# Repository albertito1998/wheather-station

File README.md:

## Table of Contents

- [Description](#description)
- [Programming](#programming)
- [About me](#about)
- [Support](#support)
- [License](#license)

---

## Description

This report will include the entire process carried out for the design and construction of a prototype of a meteorological station where data on different environmental variables will be collected for subsequent analysis.

The creation of the prototype, the different electronic components needed, the communications infrastructure, the necessary programming code and the creation of a user interface will be discussed in order to view the data collected on a web page.

The project has been carried out in a self-taught way thanks to the material provided by the Library of the Carlos III University of Madrid and the Internet and consultations made to professors, under the supervision of my TFM professor.

 * [See The complete master thesis:](-------) - Bachelor Thesis uploaded in format PDF.
 
 * [Electrical design:](https://github.com/albertito1998/wheather-station/tree/master/Eagle) - Electrical connections.

## Programming
 * [C++](https://isocpp.org/) - Programming language.
 * [JavaScript](https://www.javascript.com/) - Programming language.
 * [Bootstrap - HTML5](https://getbootstrap.com/) - A modern responsive front-end framework
 * [Firebase](https://firebase.google.com/?hl=es-419) - Google Cloud Platform

## Microprocessors and communication
 * [Esp32](https://www.espressif.com/en/products/socs/esp32) - Espressif
* [Lora](https://heltec.org/) - Heltec

## Sensors
- BMP180
- CCS811
- INA226
- DHT22
- RAIN GAUGE AND ANEMOMETER

**Real Data Display**
Thanks to the Firebase ICloud platform, data can be displayed in dynamic charts using its Realtime Database utility.

## Website
[Go to the website!! ](https://wheather-station-18cb0.web.app/)

## About 

Industrial engineering student at Carlos III University. Passion for technology, especially electronics, programming and the world of IoT!. See my CV in the following link: [CV ](https://github.com/albertito1998/SeedbedwebsiteApp/blob/master/photos/Alberto%20G%C3%B3mez%20Zueco.pdf)

## Support

Reach out to me at one of the following places!

- Linkedin at <a href="https://www.linkedin.com/in/alberto-gomez-zueco-995538179/" target="_blank">`Linkedin`</a>
- Instagram at <a href="https://www.instagram.com/alber_gz/" target="_blank">`Instagram`</a>

---

## License

- **[MIT license](http://opensource.org/licenses/mit-license.php)**
- Copyright 2022 © <a href="/LICENSE" target="_blank">MIT LICENSE ALBERTO GÓMEZ</a>.

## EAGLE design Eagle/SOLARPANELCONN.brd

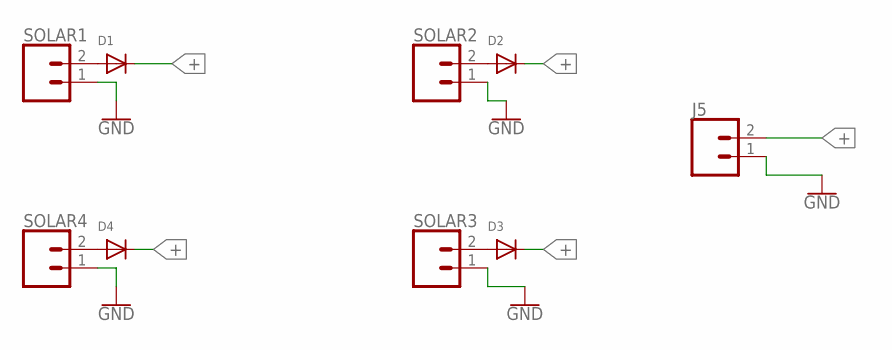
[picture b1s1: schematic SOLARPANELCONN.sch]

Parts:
D1, D2, D3, D4: DIODESOD-123; SOD-123
J5: CONN_02; 1X02
SOLAR1, SOLAR2, SOLAR3, SOLAR4: CONN_02; 1X02

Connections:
+: D1.C, D2.C, D3.C, D4.C, J5.2
GND: J5.1, SOLAR1.1, SOLAR2.1, SOLAR3.1, SOLAR4.1
unnamed: D1.A, SOLAR1.2
unnamed: D4.A, SOLAR4.2
unnamed: D3.A, SOLAR3.2
unnamed: D2.A, SOLAR2.2

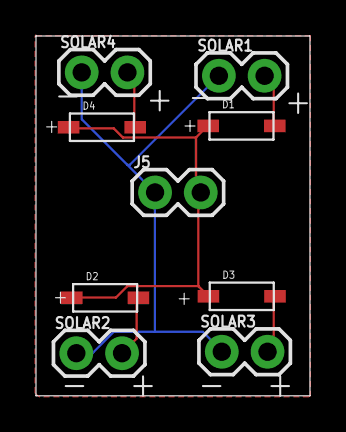
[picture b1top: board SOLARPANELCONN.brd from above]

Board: 2 copper layers, 15.2 x 20.0 mm, 9 parts (0 on the bottom side), 6 nets.

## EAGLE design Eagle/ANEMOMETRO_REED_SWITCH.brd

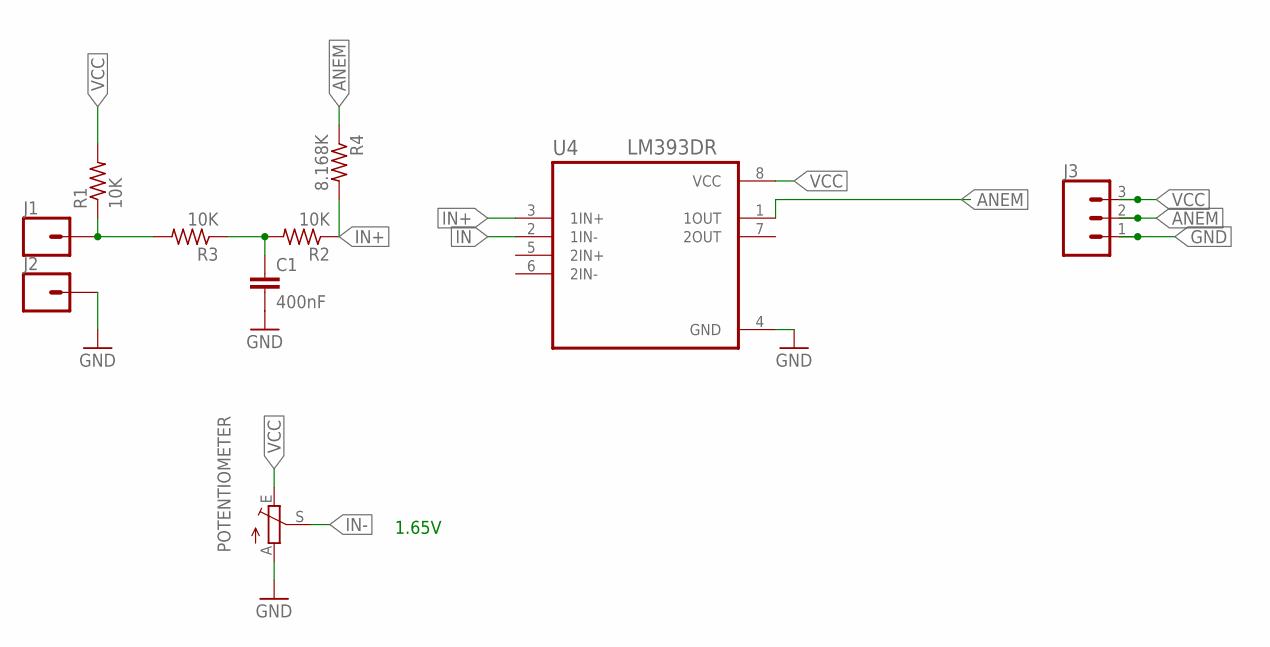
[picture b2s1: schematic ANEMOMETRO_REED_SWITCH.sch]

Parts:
C1: 400nF; C0603
J1, J2: CONN_01PTH_NO_SILK_YES_STOP; 1X01_NO_SILK
J3: CONN_03JST-PTH-VERT; JST-3-PTH-VERT
POTENTIOMETER: TRIM_EU-S64W; S64W
R1, R2, R3: 10K; R0603
R4: 8.168K; R0603
U4: LM393DR; SOIC127P599X175-8N

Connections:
ANEM: J3.2, R4.1, U4.1 (1OUT)
GND: C1.2, J2.1, J3.1, POTENTIOMETER.A, U4.4 (GND)
IN: U4.2 (1IN-)
IN+: R2.1, R4.2, U4.3 (1IN+)
IN-: POTENTIOMETER.S
unnamed: C1.1, R2.2, R3.1
unnamed: J1.1, R1.1, R3.2
VCC: J3.3, POTENTIOMETER.E, R1.2, U4.8 (VCC)

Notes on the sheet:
1.65V

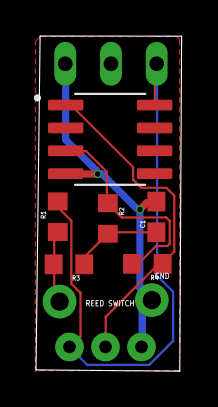
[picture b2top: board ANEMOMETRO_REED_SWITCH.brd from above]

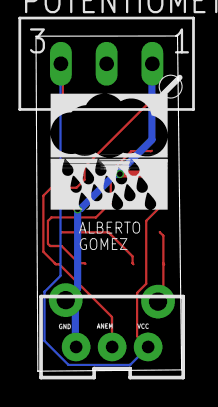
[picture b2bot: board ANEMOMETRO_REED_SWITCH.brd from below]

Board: 2 copper layers, 8.1 x 18.6 mm, 10 parts (2 on the bottom side), 6 nets.

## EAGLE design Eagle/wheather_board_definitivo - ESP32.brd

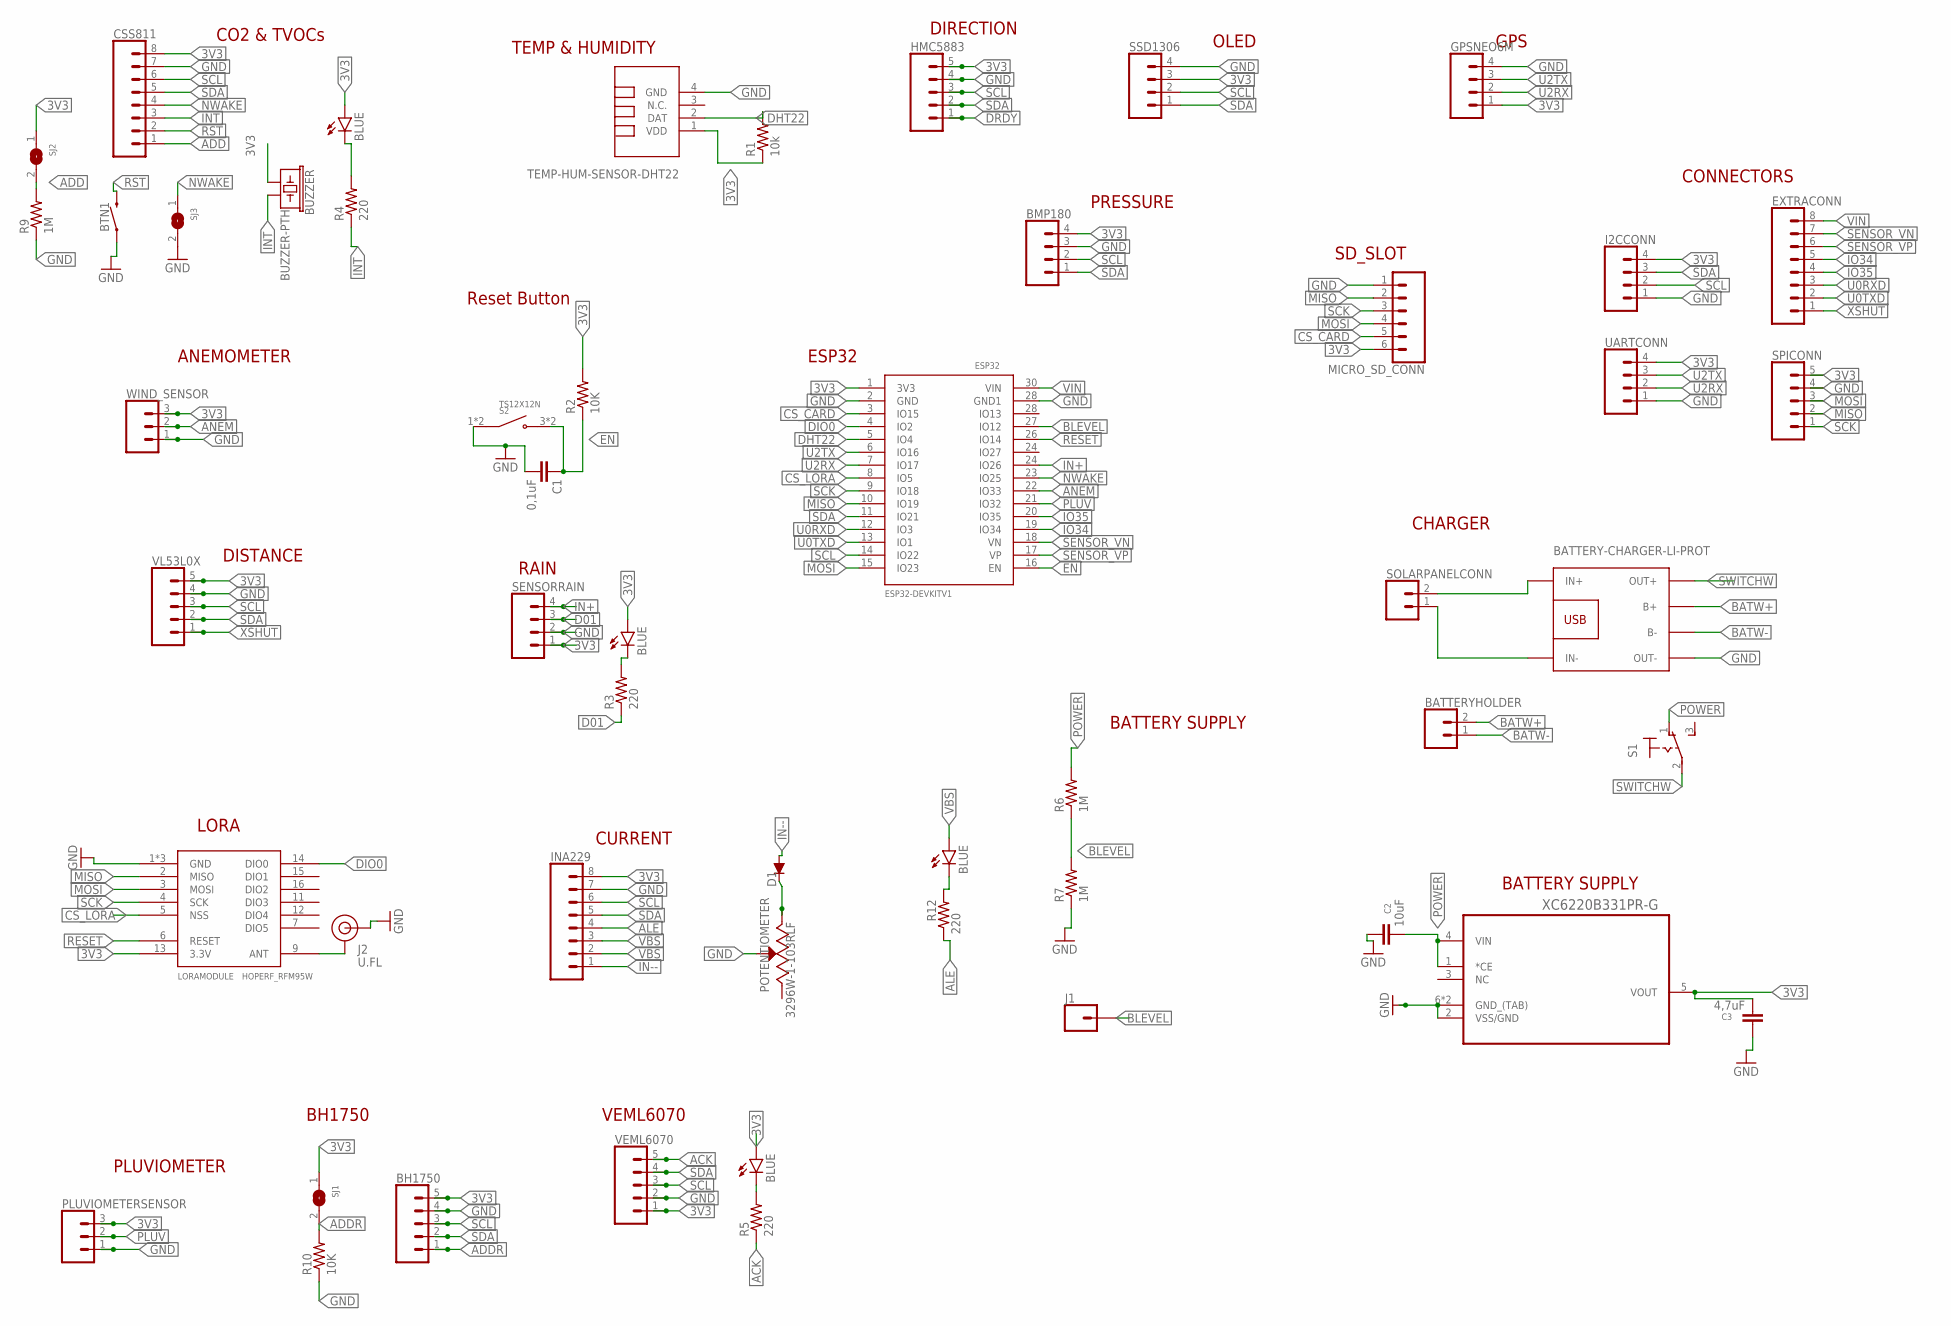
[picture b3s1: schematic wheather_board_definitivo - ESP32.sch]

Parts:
BATTERYCONN: BATTERY-CHARGER-LI-PROT
BATTERYHOLDER: CONN_02LOCK; 1X02_LOCK
BH1750: CONN_05; 1X05
BMP180: CONN_04; 1X04
BTN1: EN; TACTILE_SWITCH_SMD_6.0X3.5MM
BUZZER: BUZZER-PTH; BUZZER-12MM
C1: 0,1uF; C0603
C2: 10uF; C0603
C3: 4,7uF; C0603
CSS811: CONN_08"; 1X08
D1: DIODE_DIODE-SOD123; DIODE_SOD123
DHT22: TEMP-HUM-SENSOR-DHT22
ESP32: ESP32DEVKITV1; ESP32-DEVKITV1
EXTRACONN: CONN_08"; 1X08
GPSNEO6M: CONN_04; 1X04
HMC5883: CONN_05JST-VERT; JST-5-PTH-VERT
I2CCONN: CONN_04; 1X04
INA229: CONN_08"; 1X08
J1: CONN_01; 1X01
J2: U.FL
LED1, LED2, LED3, LED4: BLUE; LED-0603
LORAMODULE: HOPERF_RFM95W
MICRO_SD_CONN: CONN_06LOCK; 1X06_LOCK
PLUVIOMETERSENSOR: CONN_03JST-PTH-VERT; JST-3-PTH-VERT
POTENTIOMETER: 3296W-1-103RLF; TRIM_3296W-1-103RLF
R1: 10k; R0603
R2, R10: 10K; R0603
R3, R4, R5, R12: 220; R0603
R6, R7, R9: 1M; R0603
S1: 320-916
S2: TS12X12N; SW_TS12X12N
SENSORRAIN: CONN_04; 1X04
SJ1, SJ2, SJ3: SOLDERJUMPER; SOLDERJUMPER_ARROW_NOPASTE
SOLARPANELCONN: CONN_02LOCK; 1X02_LOCK
SPICONN: CONN_05; 1X05
SSD1306: CONN_04; 1X04
UARTCONN: CONN_04; 1X04
VEML6070: CONN_05; 1X05
VL53L0X: CONN_05JST-VERT; JST-5-PTH-VERT
WIND_SENSOR: CONN_03JST-PTH-VERT; JST-3-PTH-VERT
XC6220B331PR-G: XC6210B332PR

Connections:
3V3: BH1750.5, BMP180.4, BUZZER.+ (1), C3.2, CSS811.8, DHT22.1 (VDD), ESP32.1 (3V3), GPSNEO6M.1, HMC5883.5, I2CCONN.4, INA229.8, LED1.A, LED2.A, LED3.A, LORAMODULE.13 (3.3V), MICRO_SD_CONN.6, PLUVIOMETERSENSOR.3, R1.1, R2.2, SENSORRAIN.1, SJ1.1, SJ2.1, SPICONN.5, SSD1306.3, UARTCONN.4, VEML6070.1, VL53L0X.5, WIND_SENSOR.3, XC6220B331PR-G.5 (VOUT)
ACK: R5.1, VEML6070.5
ADD: CSS811.1, R9.2, SJ2.2
ADDR: BH1750.1, R10.2, SJ1.2
ALE: INA229.4, R12.1
ANEM: ESP32.22 (IO33), WIND_SENSOR.2
BATW+: BATTERYCONN.B+, BATTERYHOLDER.2
BATW-: BATTERYCONN.B-, BATTERYHOLDER.1
BLEVEL: ESP32.27 (IO12), J1.1, R6.1, R7.2
CS_CARD: ESP32.3 (IO15), MICRO_SD_CONN.5
CS_LORA: ESP32.8 (IO5), LORAMODULE.5 (NSS)
D01: R3.1, SENSORRAIN.3
DHT22: DHT22.2 (DAT), ESP32.5 (IO4), R1.2
DIO0: ESP32.4 (IO2), LORAMODULE.14 (DIO0)
DRDY: HMC5883.1
EN: C1.1, ESP32.16 (EN), R2.1, S2.3 (3_4), S2.4 (3_4)
GND: BATTERYCONN.OUT-, BH1750.4, BMP180.3, BTN1.1, C1.2, C2.1, C3.1, CSS811.7, DHT22.4 (GND), ESP32.2 (GND), ESP32.28 (IO13), GPSNEO6M.4, HMC5883.4, I2CCONN.1, INA229.7, J2.FEED (SIGNAL), LORAMODULE.1 (GND), LORAMODULE.8 (GND), LORAMODULE.10 (GND), MICRO_SD_CONN.1, PLUVIOMETERSENSOR.1, POTENTIOMETER.2 (WIPER), R7.1, R9.1, R10.1, S2.1 (1_2), S2.2 (1_2), SENSORRAIN.2, SJ3.2, SPICONN.4, SSD1306.4, UARTCONN.1, VEML6070.2, VL53L0X.4, WIND_SENSOR.1, XC6220B331PR-G.2 (VSS/GND), XC6220B331PR-G.6 (GND_(TAB)), XC6220B331PR-G.TAB (GND_(TAB))
IN+: ESP32.24 (IO27), SENSORRAIN.4
IN++: D1.C, POTENTIOMETER.3 (CW)
IN--: D1.A, INA229.1
INT: BUZZER.- (2), CSS811.3, R4.1
IO34: ESP32.19 (IO34), EXTRACONN.5
IO35: ESP32.20 (IO35), EXTRACONN.4
MISO: ESP32.10 (IO19), LORAMODULE.2 (MISO), MICRO_SD_CONN.2, SPICONN.2
MOSI: ESP32.15 (IO23), LORAMODULE.3 (MOSI), MICRO_SD_CONN.4, SPICONN.3
unnamed: LED2.C, R4.2
unnamed: LED1.C, R3.2
unnamed: BATTERYCONN.IN-, SOLARPANELCONN.1
unnamed: BATTERYCONN.IN+, SOLARPANELCONN.2
unnamed: LED3.C, R5.2
unnamed: LED4.C, R12.2
unnamed: J2.1 (GND), J2.2 (GND), LORAMODULE.9 (ANT)
NWAKE: CSS811.4, ESP32.23 (IO25), SJ3.1
PLUV: ESP32.21 (IO32), PLUVIOMETERSENSOR.2
POWER: C2.2, R6.2, S1.1 (O), XC6220B331PR-G.1 (*CE), XC6220B331PR-G.4 (VIN)
RESET: ESP32.26 (IO14), LORAMODULE.6 (RESET)
RST: BTN1.2, CSS811.2
SCK: ESP32.9 (IO18), LORAMODULE.4 (SCK), MICRO_SD_CONN.3, SPICONN.1
SCL: BH1750.3, BMP180.2, CSS811.6, ESP32.14 (IO22), HMC5883.3, I2CCONN.2, INA229.6, SSD1306.2, VEML6070.3, VL53L0X.3
SDA: BH1750.2, BMP180.1, CSS811.5, ESP32.11 (IO21), HMC5883.2, I2CCONN.3, INA229.5, SSD1306.1, VEML6070.4, VL53L0X.2
SENSOR_VN: ESP32.18 (VN), EXTRACONN.7
SENSOR_VP: ESP32.17 (VP), EXTRACONN.6
SWITCHW: BATTERYCONN.OUT+, S1.2
U0RXD: ESP32.12 (IO3), EXTRACONN.3
U0TXD: ESP32.13 (IO1), EXTRACONN.2
U2RX: ESP32.7 (IO17), GPSNEO6M.2, UARTCONN.2
U2TX: ESP32.6 (IO16), GPSNEO6M.3, UARTCONN.3
VBS: INA229.2, INA229.3, LED4.A
VIN: ESP32.30 (VIN), EXTRACONN.8
XSHUT: EXTRACONN.1, VL53L0X.1

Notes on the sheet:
BATTERY SUPPLY
Reset Button
BH1750
TEMP & HUMIDITY
CO2 & TVOCs
ANEMOMETER
ESP32
CHARGER
GPS
PRESSURE
SD_SLOT
OLED
VEML6070
CURRENT
LORA
DISTANCE
RAIN
DIRECTION
PLUVIOMETER
CONNECTORS

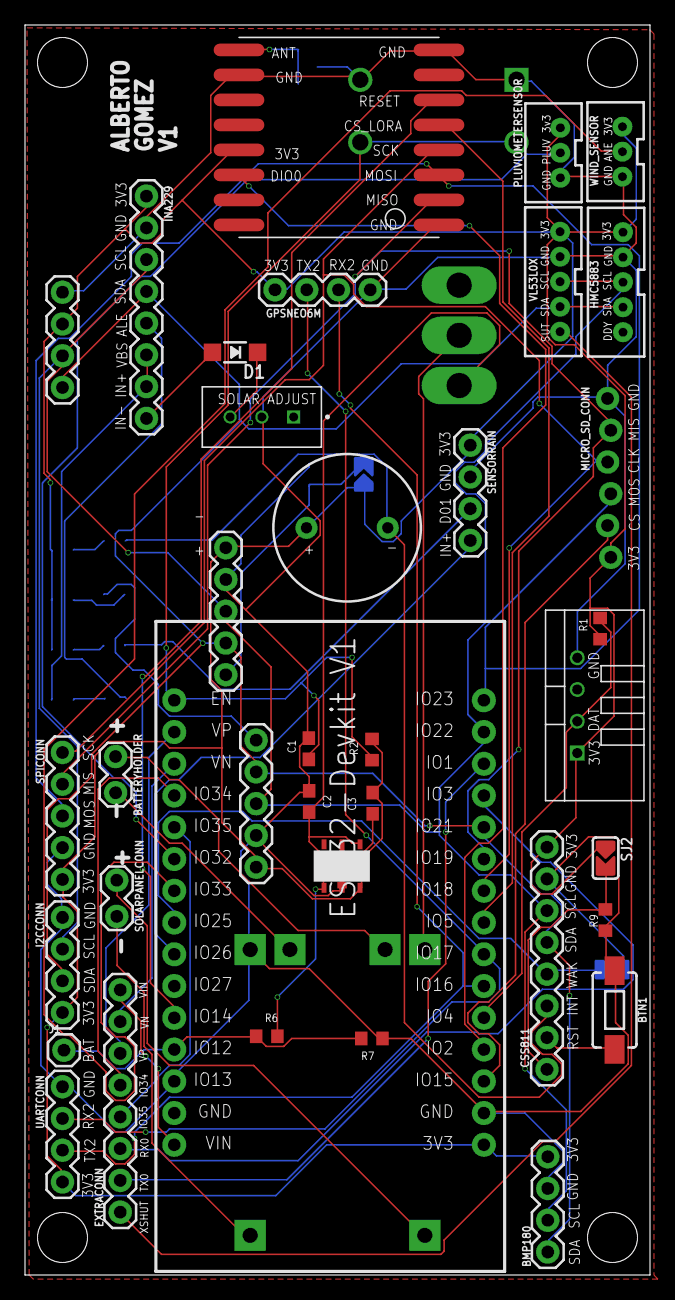
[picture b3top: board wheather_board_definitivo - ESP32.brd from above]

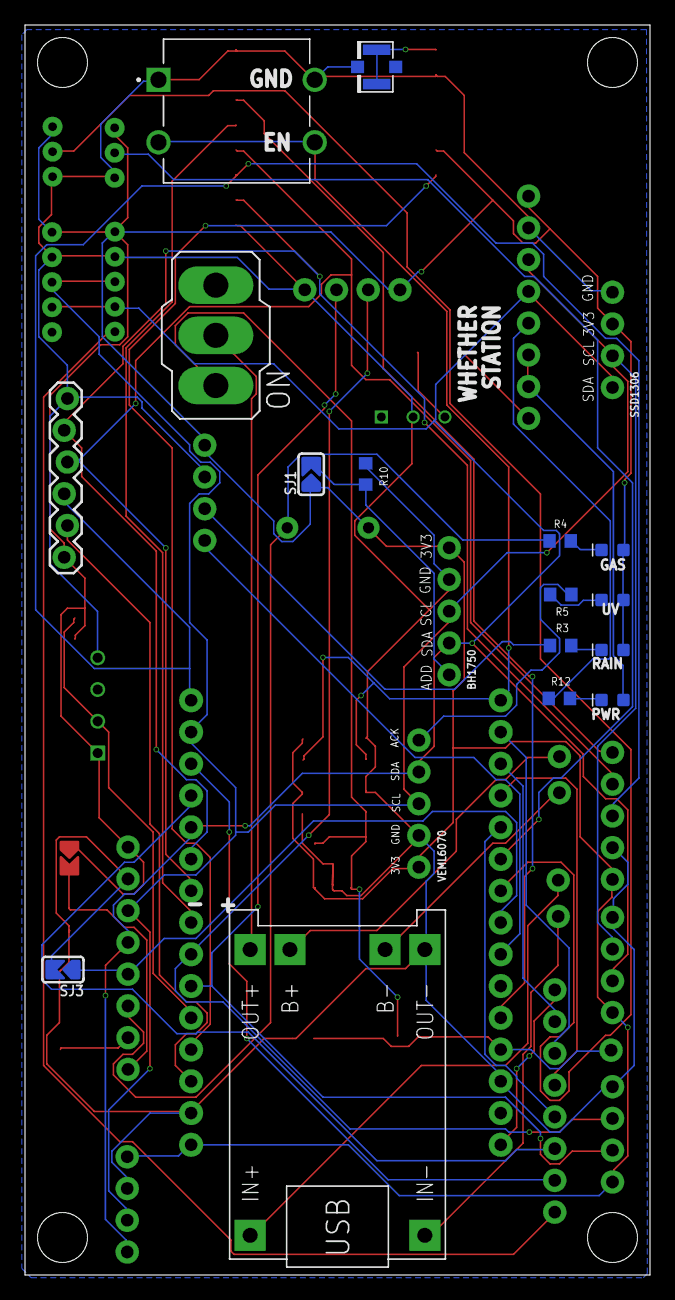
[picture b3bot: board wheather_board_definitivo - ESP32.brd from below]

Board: 2 copper layers, 50.0 x 100.0 mm, 52 parts (16 on the bottom side), 49 nets.

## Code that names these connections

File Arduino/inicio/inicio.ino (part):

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#define SCREEN_WIDTH 128 // OLED display width, in pixels
#define SCREEN_HEIGHT 64 // OLED display height, in pixels
#define DHTPIN 4     // Digital pin connected to the DHT sensor
#define DHTTYPE DHT22     // DHT22 (AM2302)
#define CS_LORA 5
#define pluv_PIN GPIO_NUM_32
#define RESET 14
#define OLED_RESET -1
#define DIO0 2
#define SD_CHIP_SELECT_PIN 15
#define spreadingFactor 10
#define codingRateDenominator 5
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  }
  Wire.begin();
  delay(100);
  esp_sleep_enable_ext0_wakeup(pluv_PIN, 1);
  esp_sleep_wakeup_cause_t wakeup_reason;

  wakeup_reason = esp_sleep_get_wakeup_cause();
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  digitalWrite(SD_CHIP_SELECT_PIN, HIGH); //SD OFF
  digitalWrite(CS_LORA, HIGH); //LORA ON
  //setup LoRa transceiver module
  LoRa.setPins(CS_LORA, RESET, DIO0);
  while (!LoRa.begin(866E6)) {
    Serial.println("Starting LoRa failed!");
    delay(500);
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
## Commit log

2021-03-26 mi primer commit
2022-06-01 Version 1
2022-06-01 Version 3
2022-06-01 Version 4
2022-06-05 Version 5
2022-06-27 Version 6
2022-06-27 Version 7
2022-06-29 Version 8
2022-06-29 Version 9
2022-06-30 Version 10
2022-07-09 Version 11

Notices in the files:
parts and their libraries:
SparkFun-Connectors: Licensing: Creative Commons ShareAlike 4.0 International - https://creativecommons.org/licenses/by-sa/4.0
diy-modules: Released under the Creative Commons Attribution 4.0 International License: http://creativecommons.org/licenses/by/4.0
